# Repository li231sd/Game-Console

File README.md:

# (NOT SO PORTABLE) Game Console!

### This project's purpose is to use an Arduino Pro Mini + a custom PCB to run a small minigame on a 0.96 OLED screen with real-time buzzer feedback!

### The whole point of the project was to learn more about CADDING and PCB design. Throughout the process, I learned to create custom symbols in KiCad's symbol editor and to run and fix DRC issues. I learned to create assemblies in SolidWorks and to use open-source CAD software for the parts I planned to use.

### Here is version #1 of my project:

### Here is version #2 which was my original final CAD but I improved it and removed the case:

### Here is version #3, the current final:

### Here is the most recent schematic of my project:

### Here is the most recent PCB of my project:

### BOM
| Name | Purpose | Quantity | Total Cost (USD) | Distributor |
|------|---------|----------|-----------------|-------------|
| [FT232RL FTDI Adapter](https://www.amazon.com/gp/product/B0FHP71BCQ/ref=ox_sc_act_title_3?smid=A3CX4TQNUXMB0L&th=1) | Connecting the Arduino Pro Mini to power and computer | 1 | $5.99 | Amazon |
| [Female Header Right Angle 0.1" 6-pin](https://www.amazon.com/Generic-Female-Header-Arduino-LilyPad/dp/B00OE8GTQ8/ref=sr_1_5?dib=eyJ2IjoiMSJ9.OMYfId4JJB0eZdjpZQFtD2b8vHiAVuLjYk6GB872IPM12OdMwTGmzGvdMlPq791cehNRzUCcW2gzgzi7IRLKBUWVLFe4ZRfsX_zvNv-tuIYqKXyvPR2U8-zQifC5jW-p_ha9amBd2QvTY7u1TlyuK-FTA1ClgemV8lKzWq9vBanH8sJ4bhrZNFvJrVMJU5aeJ0iDKp3yy43VkOBRvqNhpsFmLptXRiEaVKlYQFLwoGg.Say9IegxEDnFFbjq5Dj256TruZsi9vu6uQreEcLFhzo&dib_tag=se&keywords=right+angle+female+header&qid=1775770965&sr=8-5) | For connecting the FTDI adapter for the Arduino Pro Mini | 1 | $9.99 | Amazon |
| [PS1240P02BT](https://www.digikey.com/en/products/detail/tdk-corporation/PS1240P02BT/935924) | Buzzer for game feel | 1 | $0.57 | Digikey |
| [PCB](https://jlcpcb.com/) | Houses all the modules | 1 | $6.70 | JLCPCB |
| [Tact Button Switch](https://www.amazon.com/DAOKI-6x6x4-3mm-664-3mm-Momentary-Tactile/dp/B07X8S99RH/ref=sr_1_6_sspa?crid=8UIWIV8EL70F&dib=eyJ2IjoiMSJ9.Df-y1WvZMX-0N8DYLXNdlZlS0lQu8fAVOZWmxxgHVq0PWZV82fgugQqbFvKjgGUO.HoXwnG4VUHuKqeCKPpmxKVAwUe76eCchVRSfuzoZF54&dib_tag=se&keywords=Push%2Bbutton%2B6mmx6mmx4.3mm&qid=1773165291&s=hi&sprefix=push%2Bbutton%2B6mmx6mmx4.3mm%2Ctools%2C128&sr=1-6-spons&sp_csd=d2lkZ2V0TmFtZT1zcF9tdGY&th=1) | Controls of the game | 1 | $4.99 | Amazon |
| [SSD1306](https://www.amazon.com/UCTRONICS-SSD1306-Self-Luminous-Display-Raspberry/dp/B072Q2X2LL/ref=pd_ybh_a_d_sccl_3/138-6471428-0838013?pd_rd_w=WufjE&content-id=amzn1.sym.67f8cf21-ade4-4299-b433-69e404eeecf1&pf_rd_p=67f8cf21-ade4-4299-b433-69e404eeecf1&pf_rd_r=GAB7MCX3YXFJCJSPVCYP&pd_rd_wg=lfuYW&pd_rd_r=41f4390e-6f47-4ed2-99bd-be0129f47c18&pd_rd_i=B072Q2X2LL&psc=1) | OLED Display | 1 | $6.99 | Amazon |
| [Arduino Pro Mini](https://www.amazon.com/Arduino-Pro-Mini-328-16MHz/dp/B004G53J5I/ref=pd_ybh_a_d_sccl_2/138-6471428-0838013?pd_rd_w=1Rg71&content-id=amzn1.sym.67f8cf21-ade4-4299-b433-69e404eeecf1&pf_rd_p=67f8cf21-ade4-4299-b433-69e404eeecf1&pf_rd_r=DMKNHCCF81W10P4MNC8D&pd_rd_wg=YTIhm&pd_rd_r=8940d3c2-13ab-4f26-811c-7a622cb94b2a&pd_rd_i=B004G53J5I&psc=1) | Brains of the console | 1 | $11.25 | Amazon |

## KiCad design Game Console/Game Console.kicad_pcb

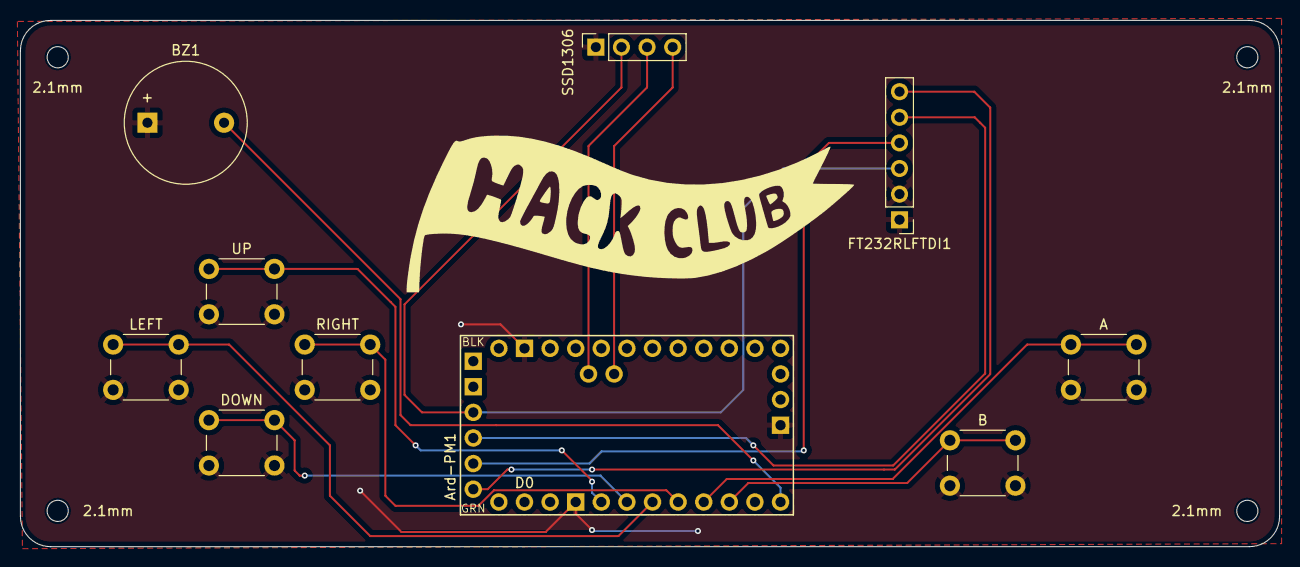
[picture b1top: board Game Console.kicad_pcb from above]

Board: 2 copper layers, 124.9 x 52.2 mm, 14 parts (0 on the bottom side), 14 nets.

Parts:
2.1mm, 2.1mm#2, 2.1mm#3, 2.1mm#4: MountingHole_2.1mm
A: SW_A; SW_PUSH_6mm_H4.3mm
Ard-PM1: Clone_Pro_Mini_Socket
B: SW_B; SW_PUSH_6mm_H4.3mm
BZ1: Buzzer; Buzzer_12x9.5RM7.6
DOWN: SW_DOWN; SW_PUSH_6mm_H4.3mm
FT232RLFTDI1: Conn_01x06_Pin; PinHeader_1x06_P2.54mm_Vertical
LEFT: SW_LEFT; SW_PUSH_6mm_H4.3mm
RIGHT: SW_RIGHT; SW_PUSH_6mm_H4.3mm
SSD1306: Conn_01x04_Socket; PinSocket_1x04_P2.54mm_Vertical
UP: SW_UP; SW_PUSH_6mm_H4.3mm

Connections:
GND: A.2, Ard-PM1.GND1 (GND), Ard-PM1.GND2 (GND), Ard-PM1.GND3 (GND), B.2, BZ1.1 (+), DOWN.2, FT232RLFTDI1.1, FT232RLFTDI1.2, LEFT.2, RIGHT.2, SSD1306.1, UP.2
unnamed: Ard-PM1.D2 (2), UP.1
unnamed: Ard-PM1.D3 (3), DOWN.1
unnamed: Ard-PM1.D4 (4), LEFT.1
unnamed: Ard-PM1.D5 (5), RIGHT.1
unnamed: A.1, Ard-PM1.D6 (6)
unnamed: Ard-PM1.D7 (7), B.1
unnamed: Ard-PM1.D9 (9), BZ1.2 (-)
unnamed: Ard-PM1.TXO, FT232RLFTDI1.4
unnamed: Ard-PM1.RXI, FT232RLFTDI1.5
unnamed: Ard-PM1.DTR, FT232RLFTDI1.6
unnamed: Ard-PM1.A5, SSD1306.3
unnamed: Ard-PM1.A4, SSD1306.4
VCC: Ard-PM1.Vcc2 (VCC), FT232RLFTDI1.3, SSD1306.2

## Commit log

2026-03-17 Enhance README with project details and images
    Expanded project description with additional learning experiences in SolidWorks and open source CADs. Added images of project versions and schematics.
2026-03-17 Enhance README with project details and BOM
    Updated project description and added Bill of Materials section.
2026-03-17 Fix total cost in the components table
2026-03-17 Rename components.csv to BOM.csv
2026-03-17 Rename hook.STEP to claw.STEP
2026-03-20 Revise project description in README.md
    Reworded project explanation for clarity and conciseness.
2026-04-09 Updated all files for the newest version of the project
